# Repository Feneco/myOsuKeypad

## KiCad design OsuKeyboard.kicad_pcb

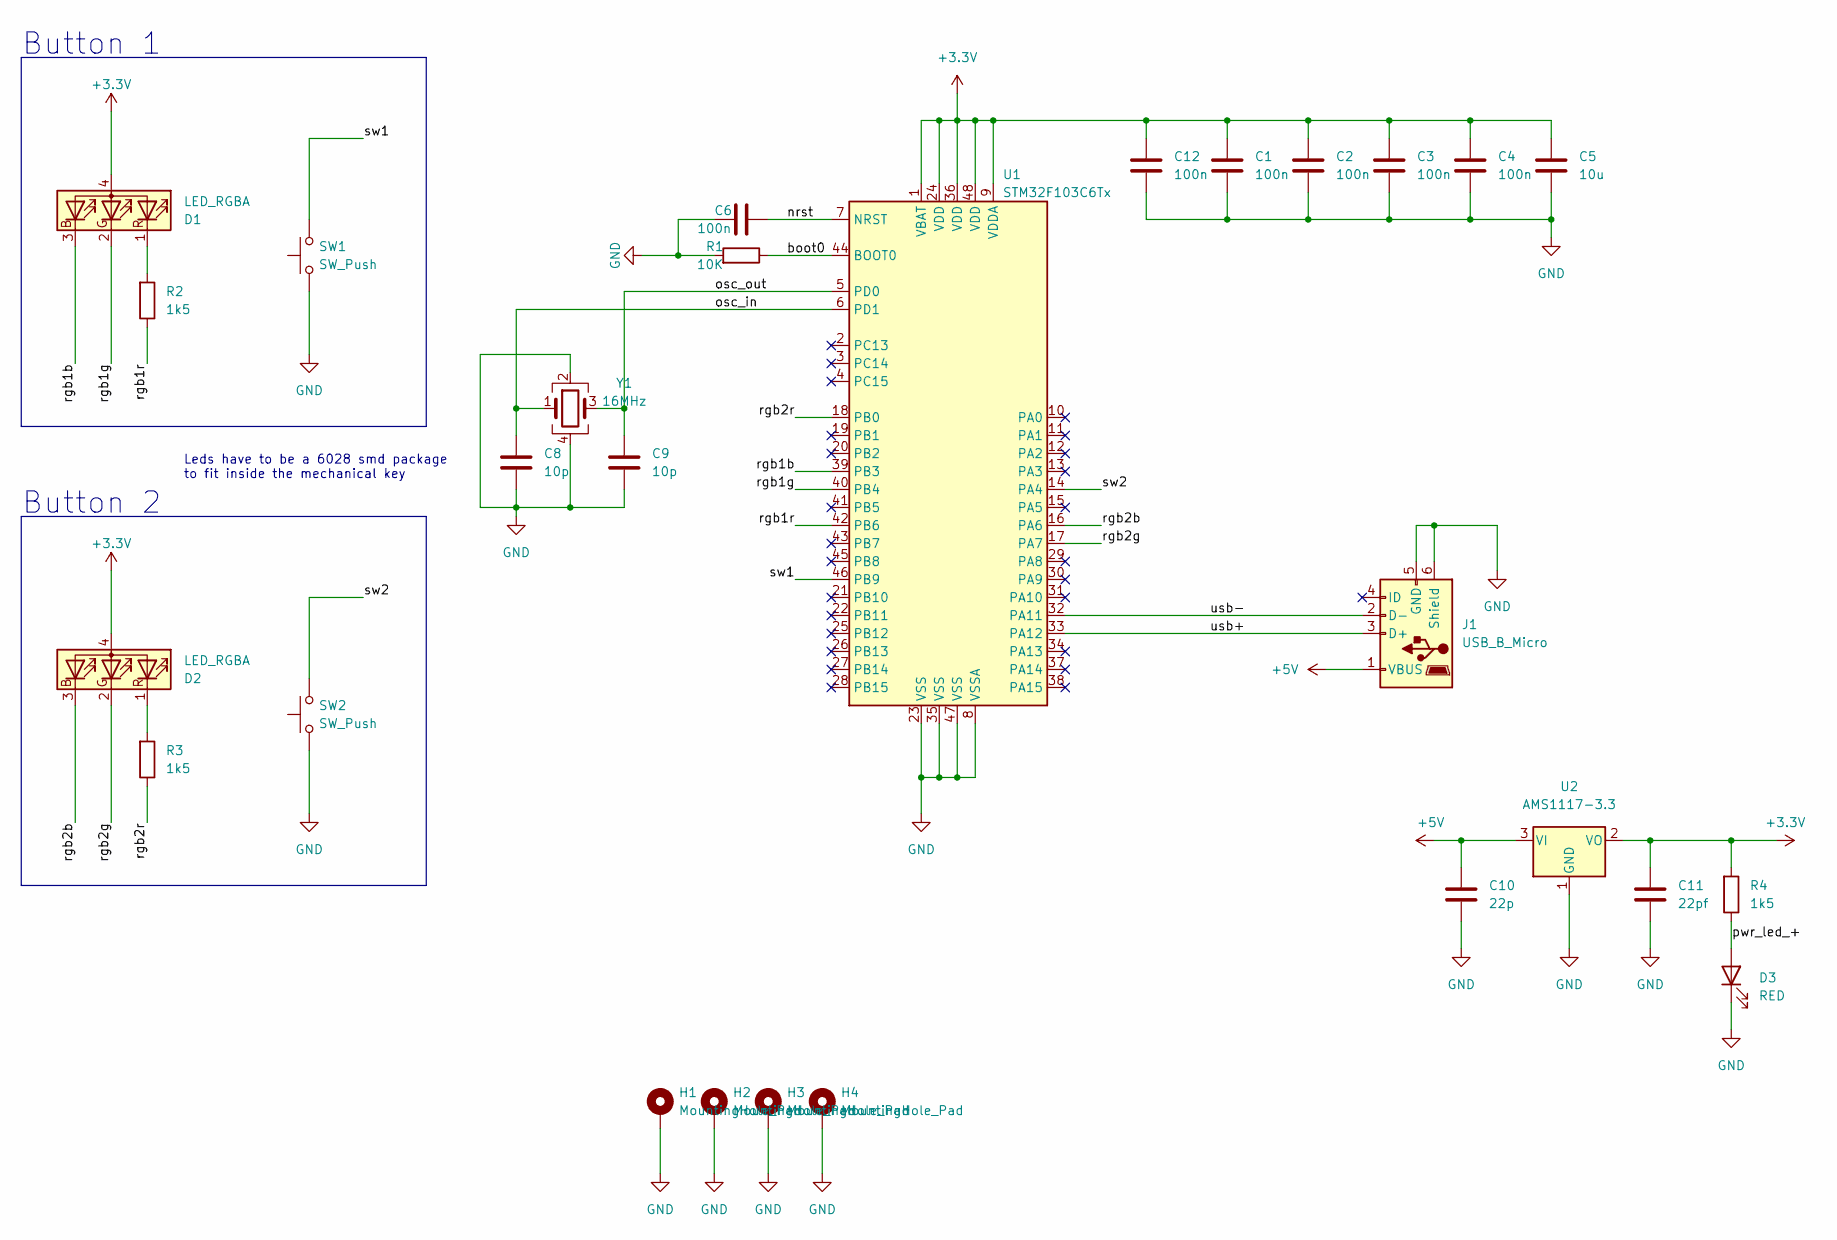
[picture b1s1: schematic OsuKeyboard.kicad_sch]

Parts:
C1, C2, C3, C4, C6, C12: 100n; C_0402_1005Metric_Pad0.74x0.62mm_HandSolder
C5: 10u; C_0402_1005Metric_Pad0.74x0.62mm_HandSolder
C8, C9: 10p; C_0402_1005Metric_Pad0.74x0.62mm_HandSolder
C10: 22p; C_0402_1005Metric_Pad0.74x0.62mm_HandSolder
C11: 22pf; C_0402_1005Metric_Pad0.74x0.62mm_HandSolder
D1, D2: LED_RGBA; LED_SK6812_EC15_1.5x1.5mm
D3: RED; LED_0402_1005Metric
H1, H2, H3, H4: MountingHole_Pad; MountingHole_2.2mm_M2_Pad
J1: USB_B_Micro; USB_Micro-B_Wuerth_629105150521_CircularHoles
R1: 10K; R_0402_1005Metric_Pad0.72x0.64mm_HandSolder
R2, R3, R4: 1k5; R_0402_1005Metric_Pad0.72x0.64mm_HandSolder
SW1, SW2: SW_Push; SW_Cherry_MX_1.00u_PCB
U1: STM32F103C6Tx; LQFP-48_7x7mm_P0.5mm
U2: AMS1117-3.3; SOT-223-3_TabPin2
Y1: 16MHz; Crystal_SMD_3225-4Pin_3.2x2.5mm

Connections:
+3.3V: C1.1, C2.1, C3.1, C4.1, C5.1, C11.1, C12.1, D1.4 (A), D2.4 (A), R4.2, U1.1 (VBAT), U1.9 (VDDA), U1.24 (VDD), U1.36 (VDD), U1.48 (VDD), U2.2 (VO)
+5V: C10.1, J1.1 (VBUS), U2.3 (VI)
/boot0: R1.1, U1.44 (BOOT0)
/nrst: C6.2, U1.7 (NRST)
/osc_in: C8.1, U1.6 (PD1), Y1.1
/osc_out: C9.1, U1.5 (PD0), Y1.3
/pwr_led_+: D3.2 (A), R4.1
/rgb1b: D1.3 (BK), U1.39 (PB3)
/rgb1g: D1.2 (GK), U1.40 (PB4)
/rgb1r: R2.1, U1.42 (PB6)
/rgb2b: D2.3 (BK), U1.16 (PA6)
/rgb2g: D2.2 (GK), U1.17 (PA7)
/rgb2r: R3.1, U1.18 (PB0)
/sw1: SW1.2, U1.46 (PB9)
/sw2: SW2.2, U1.14 (PA4)
/usb+: J1.3 (D+), U1.33 (PA12)
/usb-: J1.2 (D-), U1.32 (PA11)
GND: C1.2, C2.2, C3.2, C4.2, C5.2, C6.1, C8.2, C9.2, C10.2, C11.2, C12.2, D3.1 (K), H1.1, H2.1, H3.1, H4.1, J1.5 (GND), J1.6 (Shield), R1.2, SW1.1, SW2.1, U1.8 (VSSA), U1.23 (VSS), U1.35 (VSS), U1.47 (VSS), U2.1 (GND), Y1.2, Y1.4
unnamed: D1.1 (RK), R2.2
unnamed: D2.1 (RK), R3.2

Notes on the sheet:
Leds have to be a 6028 smd package to fit inside the mechanical key
Button 1
Button 2

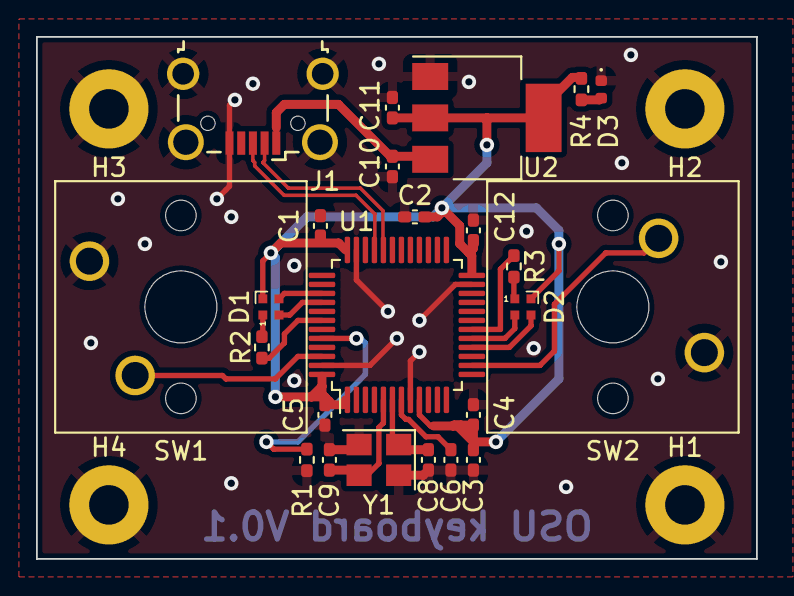
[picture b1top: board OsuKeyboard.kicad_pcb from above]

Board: 2 copper layers, 40.0 x 29.0 mm, 28 parts (0 on the bottom side), 20 nets.

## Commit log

2022-10-10 Changed MCU and layout
2022-11-30 simplified and made pcb smaller
